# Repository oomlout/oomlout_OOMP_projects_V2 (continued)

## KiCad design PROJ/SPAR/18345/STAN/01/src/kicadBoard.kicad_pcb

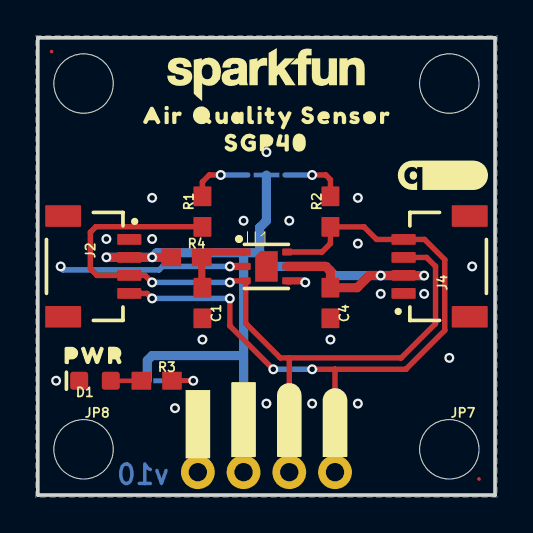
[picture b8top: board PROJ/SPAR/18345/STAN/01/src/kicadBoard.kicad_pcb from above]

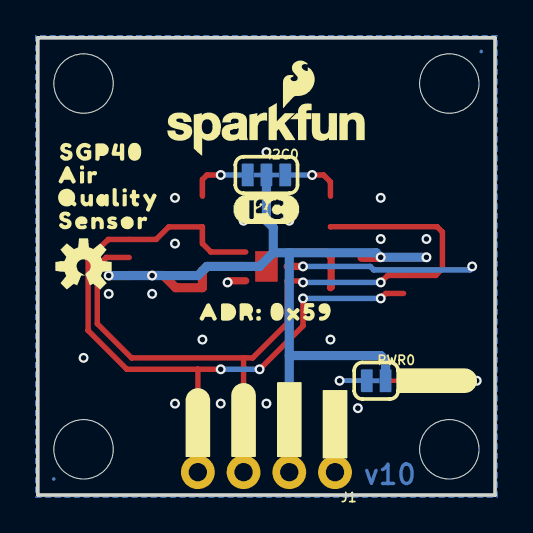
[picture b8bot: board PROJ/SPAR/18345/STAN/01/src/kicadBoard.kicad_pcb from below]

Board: 2 copper layers, 25.4 x 25.4 mm, 48 parts (19 on the bottom side), 9 nets.

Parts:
C1, C4: 1.0uF; 0603
D1: RED; LED-0603
FRAME1: FRAME-LETTER; CREATIVE_COMMONS
I2C0: JUMPER-SMT_3_2-NC_TRACE_SILK; SMT-JUMPER_3_2-NC_TRACE_SILK
J1: DNP; 1X04_NO_SILK
J2, J4: QWIIC_RA; JST04_1MM_RA
JP1, JP2, JP5, JP6: FIDUCIAL0.2MM; FIDUCIAL-0.2MM
JP3, JP4, JP7, JP8: STAND-OFF
LOGO1: SPECIAL_INSTRUCTIONS-ORDERING; ORDERING_INSTRUCTIONS
LOGO2: QWIIC_LOGO_5MM; QWIIC_5MM
LOGO3, LOGO6: SFE_LOGO_NAME.1_INCH; SFE_LOGO_NAME_.1
LOGO4: SFE_LOGO_FLAME.1_INCH; SFE_LOGO_FLAME_.1
LOGO5: OSHW-LOGOS; OSHW-LOGO-S
PWR0: JUMPER-SMT_2_NC_TRACE_SILK; SMT-JUMPER_2_NC_TRACE_SILK
R1, R2: 4.7k; 0603
R3: 1k; 0603
R4: 4.7; 0603
U1: SGP40
U$1, U$33: #GND#0
U$2, U$34: #3#3V#0
U$3, U$35: #SDA#0
U$4, U$36: #SCL#0
U$5: PWR0
U$6: #PWR#0
U$15: I2C
U$19, U$20: SGP400
U$23, U$24: AIR0
U$25, U$28: QUALITY0
U$29, U$30: SENSOR0
U$31: ADR#_0X590

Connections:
3.3V: C4.1, I2C0.2, J1.2, J2.2, J4.2, PWR0.2, R4.1, U1.5
GND: C1.2, C4.2, D1.C, J1.1, J2.1, J4.1, U1.2, U1.4, U1.DIEPAD
unnamed: PWR0.1, R3.2
unnamed: I2C0.3, R1.2
unnamed: D1.A, R3.1
unnamed: I2C0.1, R2.2
unnamed: C1.1, R4.2, U1.1
SCL: J1.4, J2.4, J4.4, R2.1, U1.6
SDA: J1.3, J2.3, J4.3, R1.1, U1.3
